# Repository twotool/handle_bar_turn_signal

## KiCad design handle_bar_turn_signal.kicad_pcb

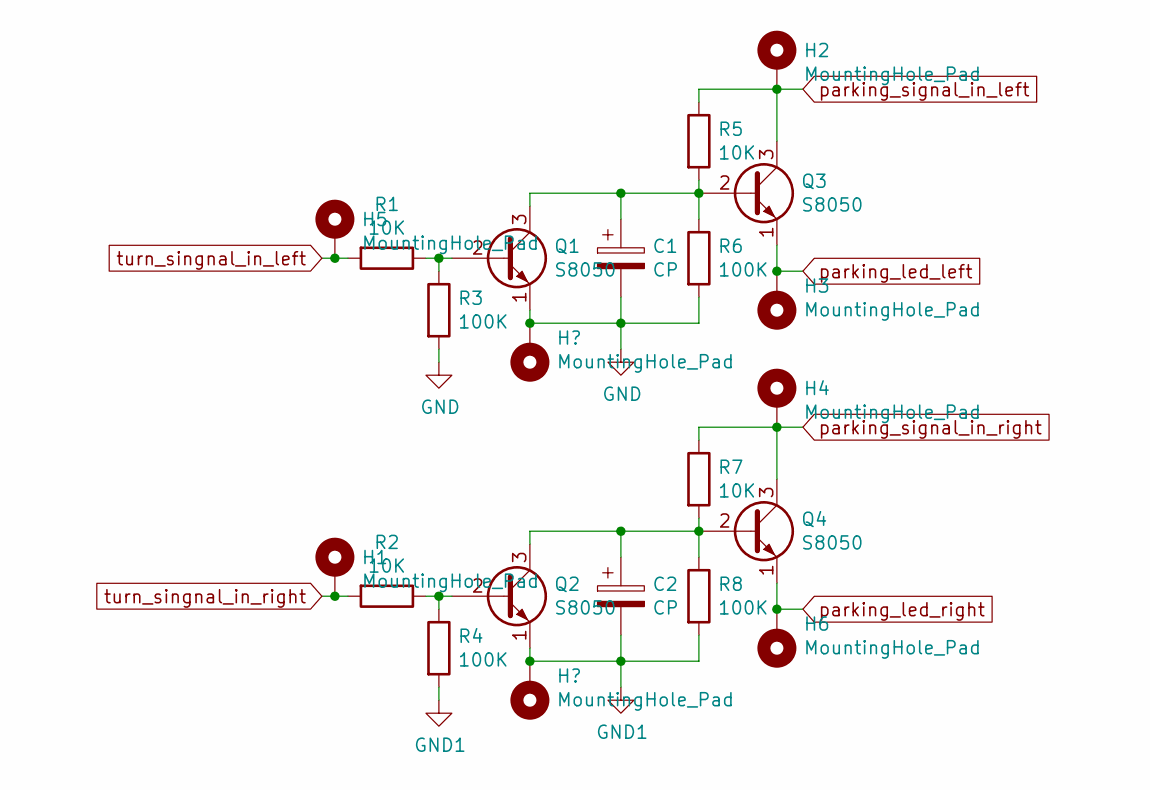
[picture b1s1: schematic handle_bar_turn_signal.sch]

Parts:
C1, C2: CP; CP_Radial_Tantal_D5.5mm_P2.50mm
H1, H2, H3, H4, H5, H6: MountingHole_Pad; MountingHole_2.2mm_M2_DIN965_Pad
Q1, Q2, Q3, Q4: S8050; TO-92L_Inline_Wide
R1, R2, R5, R7: 10K; R_Axial_DIN0207_L6.3mm_D2.5mm_P10.16mm_Horizontal
R3, R4, R6, R8: 100K; R_Axial_DIN0207_L6.3mm_D2.5mm_P10.16mm_Horizontal

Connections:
GND: C1.2, Q1.1 (E), R3.2, R6.2; also elsewhere on the board
GND1: C2.2, Q2.1 (E), R4.2, R8.2; also elsewhere on the board
unnamed: C1.1, Q1.3 (C), Q3.2 (B), R5.2, R6.1
unnamed: C2.1, Q2.3 (C), Q4.2 (B), R7.2, R8.1
unnamed: Q1.2 (B), R1.1, R3.1
unnamed: Q2.2 (B), R2.1, R4.1
parking_led_left: H3.1, Q3.1 (E)
parking_led_right: H6.1, Q4.1 (E)
parking_signal_in_left: H2.1, Q3.3 (C), R5.1
parking_signal_in_right: H4.1, Q4.3 (C), R7.1
turn_singnal_in_left: H5.1, R1.2
turn_singnal_in_right: H1.1, R2.2

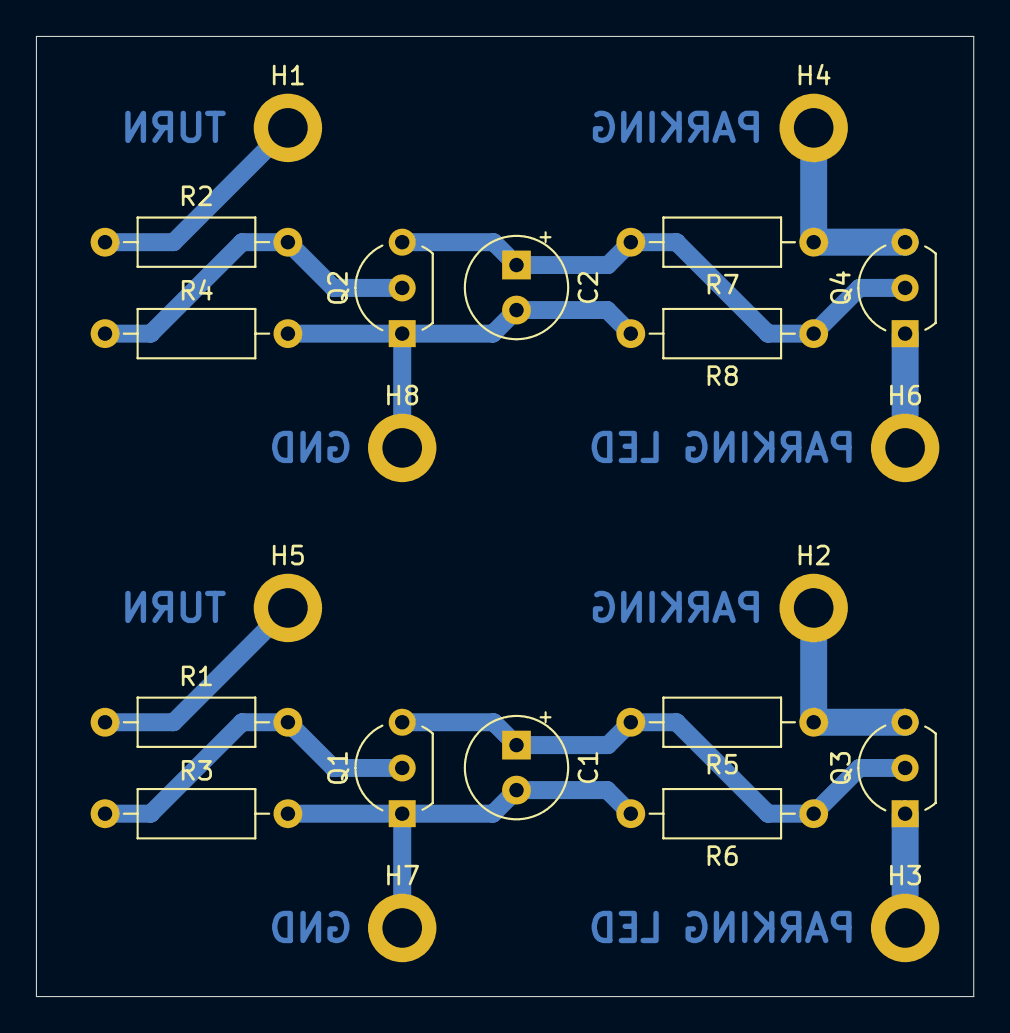
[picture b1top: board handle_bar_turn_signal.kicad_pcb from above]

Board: 2 copper layers, 52.1 x 53.3 mm, 22 parts (0 on the bottom side), 12 nets.

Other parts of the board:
H7, H8: MountingHole_Pad; MountingHole_2.2mm_M2_DIN965_Pad

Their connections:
GND: H7.1; also elsewhere on the board
GND1: H8.1; also elsewhere on the board
